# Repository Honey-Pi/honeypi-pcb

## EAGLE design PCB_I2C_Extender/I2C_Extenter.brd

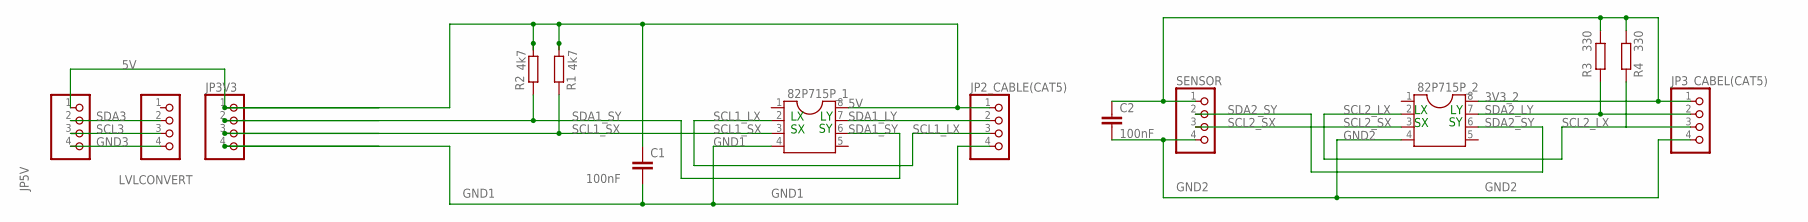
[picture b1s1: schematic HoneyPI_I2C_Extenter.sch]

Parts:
82P715P_1, 82P715P_2: DIL8; DIL08
C1, C2: 100nF; C050-045X075
JP2_CABLE(CAT5), JP3V3, JP3_CABEL(CAT5), JP5V: PINHD-1X4; 1X04
LVLCONVERT: PINHD-1X4; 1X04
R1, R2: 4k7; 0207/7
R3, R4: 330; 0207/7
SENSOR: PINHD-1X4; 1X04

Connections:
3V3_2: 82P715P_2.8, C2.1, JP3_CABEL(CAT5).1, R3.1, R4.1, SENSOR.1
5V: 82P715P_1.8, C1.1, JP2_CABLE(CAT5).1, JP3V3.1, JP5V.1, R1.1, R2.1
GND1: 82P715P_1.4, C1.2, JP2_CABLE(CAT5).4, JP3V3.4
GND2: 82P715P_2.4, C2.2, JP3_CABEL(CAT5).4, SENSOR.4
GND3: JP5V.4, LVLCONVERT.4
SCL1_LX: 82P715P_1.2, JP2_CABLE(CAT5).3
SCL1_SX: 82P715P_1.3, JP3V3.3, R1.2
SCL2_LX: 82P715P_2.2, JP3_CABEL(CAT5).3, R4.2
SCL2_SX: 82P715P_2.3, SENSOR.3
SCL3: JP5V.3, LVLCONVERT.3
SDA1_LY: 82P715P_1.7, JP2_CABLE(CAT5).2
SDA1_SY: 82P715P_1.6, JP3V3.2, R2.2
SDA2_LY: 82P715P_2.7, JP3_CABEL(CAT5).2, R3.2
SDA2_SY: 82P715P_2.6, SENSOR.2
SDA3: JP5V.2, LVLCONVERT.2

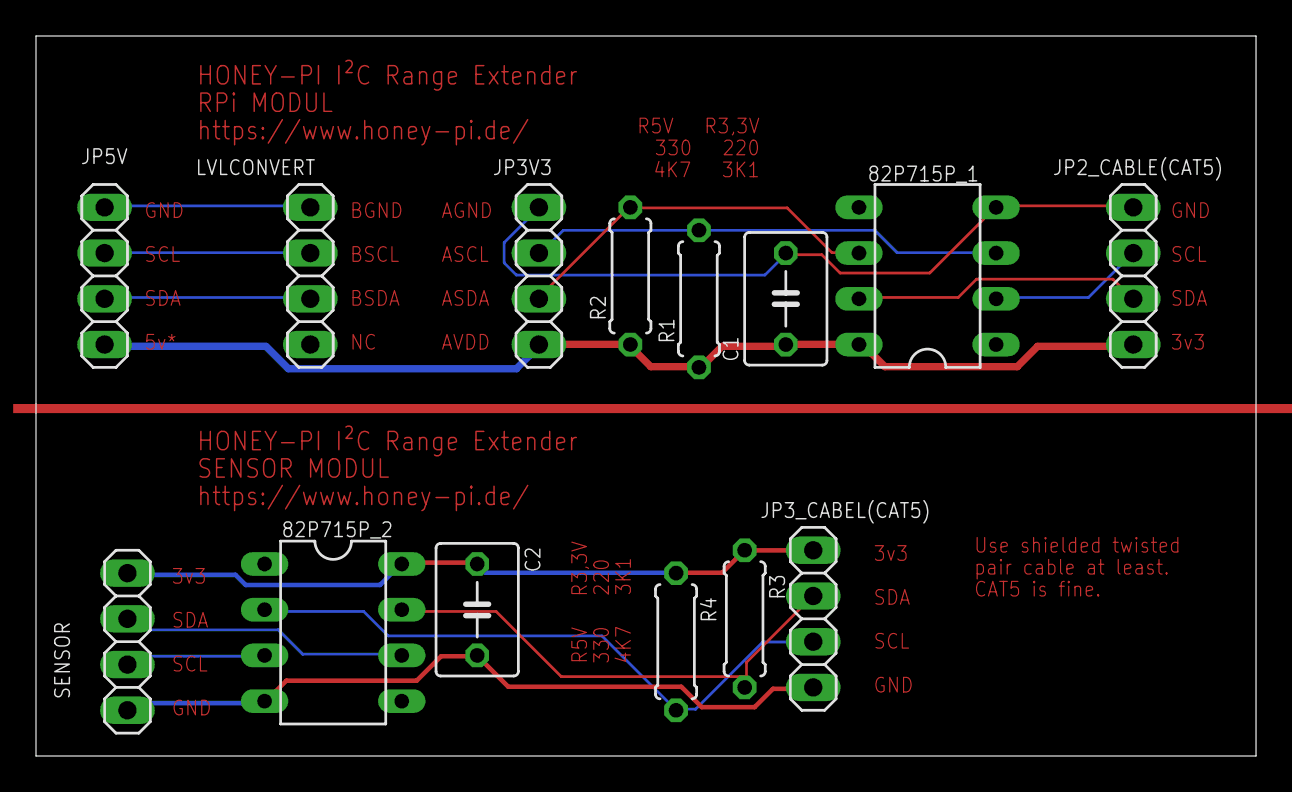
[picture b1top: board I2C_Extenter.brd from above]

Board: 2 copper layers, 67.8 x 40.0 mm, 14 parts (0 on the bottom side), 15 nets.

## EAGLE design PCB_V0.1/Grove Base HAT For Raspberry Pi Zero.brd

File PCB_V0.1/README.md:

# honeypi-pcb V0.1

Printed circuit board (PCB) for the Raspberry Pi to connect various sensors. To avoid the use of jumper cables.

## V0.1 [link](./PCB_V0.1)
Check out this [blogpost](https://www.honey-pi.de/teil-3-adapter-lk-fuer-grove-stecker/) about the grove connector board for the Raspberry Zero.
You can upload the [gerber file](./Grove%20Base%20HAT%20For%20Raspberry%20Pi%20Zero_2019-01-13.zip) to [this manufactory service](https://jlcpcb.com/quote). 10 pieces of this board cost about 7 € with delivery. 

### Pictures

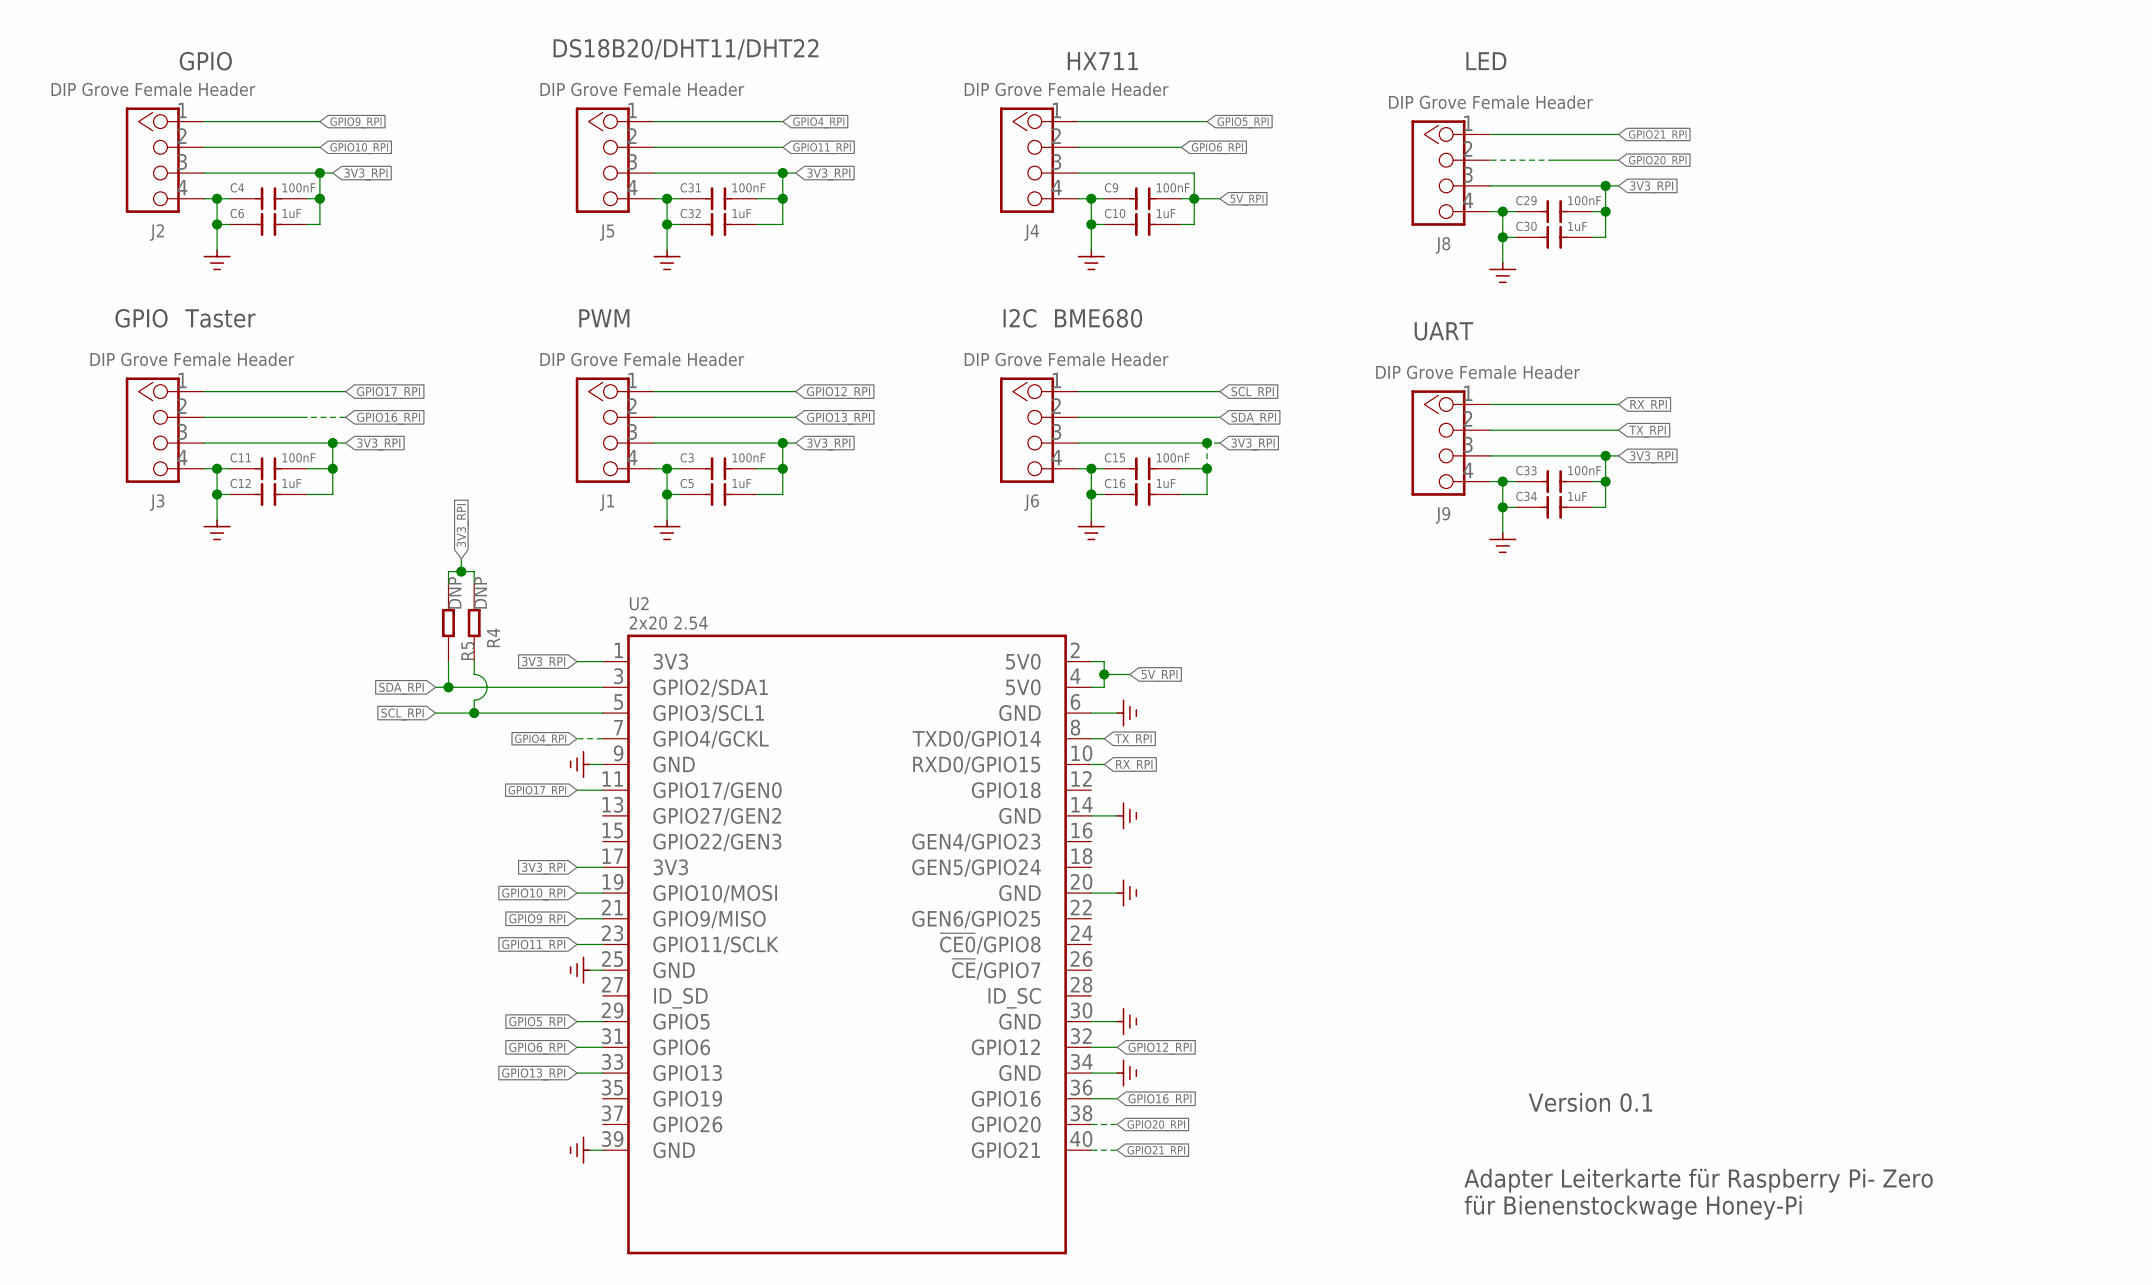
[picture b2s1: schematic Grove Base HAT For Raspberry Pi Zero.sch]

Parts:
C3, C4, C9, C11, C15, C29, C31, C33: 100nF; C0603
C5, C6, C10, C12, C16, C30, C32, C34: 1uF; C0603
J1, J2, J3, J4, J5, J6, J8, J9: DIP Grove Female Header; HW4-2.0
R4, R5: DNP; R0603
U2: 2x20 2.54; RASPBERRYPI_BASTELSTUBE_V13_RASPI_BOARD_B+_FULL

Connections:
3V3_RPI: C3.2, C4.2, C5.2, C6.2, C11.2, C12.2, C15.2, C16.2, C29.2, C30.2, C31.2, C32.2, C33.2, C34.2, J1.3, J2.3, J3.3, J5.3, J6.3, J8.3, J9.3, R4.2, R5.2, U2.1 (3V3), U2.17 (3V3)
5V_RPI: C9.2, C10.2, J4.3, U2.2 (5V0), U2.4 (5V0)
GND: C3.1, C4.1, C5.1, C6.1, C9.1, C10.1, C11.1, C12.1, C15.1, C16.1, C29.1, C30.1, C31.1, C32.1, C33.1, C34.1, J1.4, J2.4, J3.4, J4.4, J5.4, J6.4, J8.4, J9.4, U2.6 (GND), U2.9 (GND), U2.14 (GND), U2.20 (GND), U2.25 (GND), U2.30 (GND), U2.34 (GND), U2.39 (GND)
GPIO4_RPI: J5.1, U2.7 (GPIO4/GCKL)
GPIO5_RPI: J4.1, U2.29 (GPIO5)
GPIO6_RPI: J4.2, U2.31 (GPIO6)
GPIO9_RPI: J2.1, U2.21 (GPIO9/MISO)
GPIO10_RPI: J2.2, U2.19 (GPIO10/MOSI)
GPIO11_RPI: J5.2, U2.23 (GPIO11/SCLK)
GPIO12_RPI: J1.1, U2.32 (GPIO12)
GPIO13_RPI: J1.2, U2.33 (GPIO13)
GPIO16_RPI: J3.2, U2.36 (GPIO16)
GPIO17_RPI: J3.1, U2.11 (GPIO17/GEN0)
GPIO20_RPI: J8.2, U2.38 (GPIO20)
GPIO21_RPI: J8.1, U2.40 (GPIO21)
RX_RPI: J9.1, U2.10 (RXD0/GPIO15)
SCL_RPI: J6.1, R4.1, U2.5 (GPIO3/SCL1)
SDA_RPI: J6.2, R5.1, U2.3 (GPIO2/SDA1)
TX_RPI: J9.2, U2.8 (TXD0/GPIO14)

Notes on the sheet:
PWM
GPIO
UART
I2C
Version 0.1
Adapter Leiterkarte für Raspberry Pi- Zero für Bienenstockwage Honey-Pi
HX711
Taster
LED
DS18B20/DHT11/DHT22
BME680

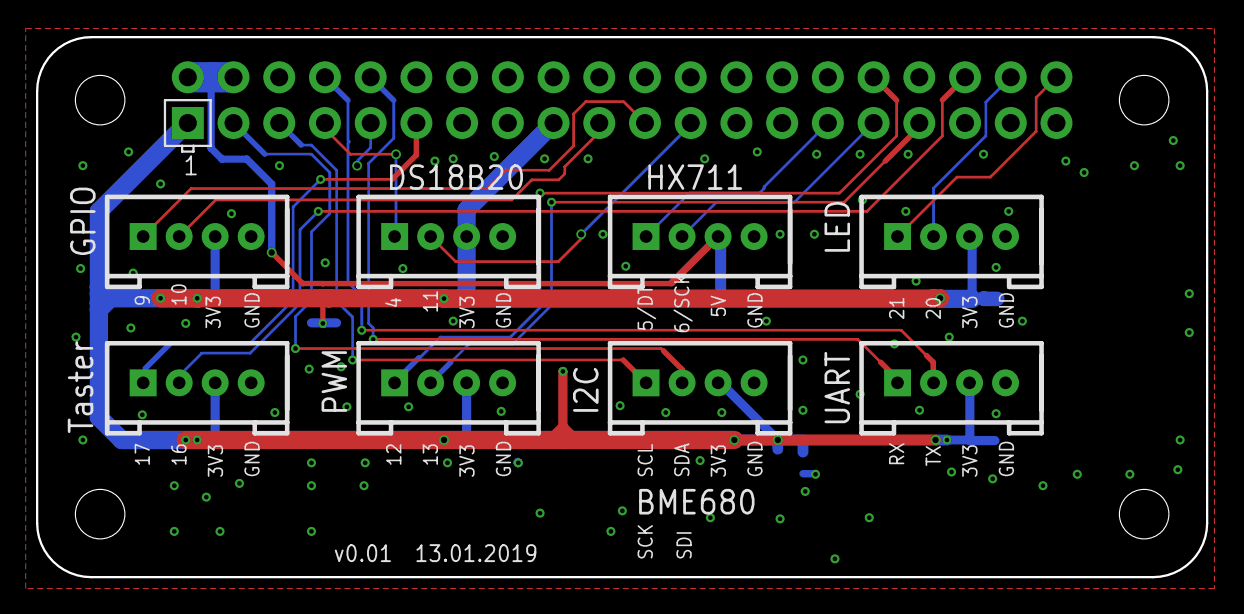
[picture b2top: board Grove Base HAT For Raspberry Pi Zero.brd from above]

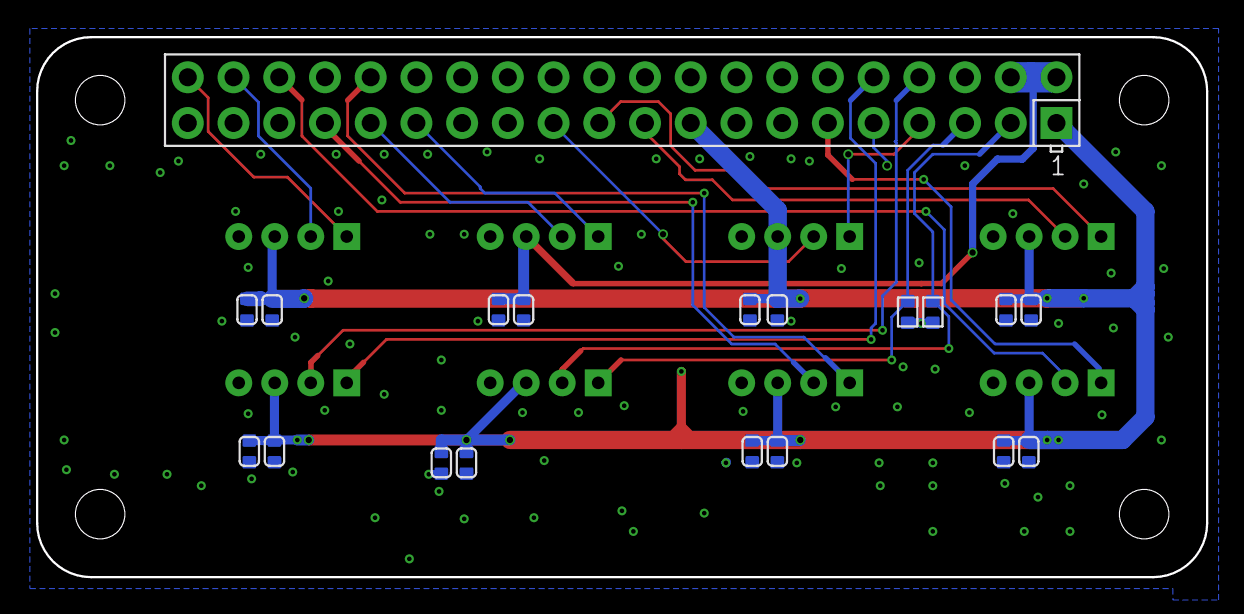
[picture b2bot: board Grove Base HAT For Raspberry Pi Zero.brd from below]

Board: 2 copper layers, 65.0 x 30.0 mm, 27 parts (18 on the bottom side), 19 nets.

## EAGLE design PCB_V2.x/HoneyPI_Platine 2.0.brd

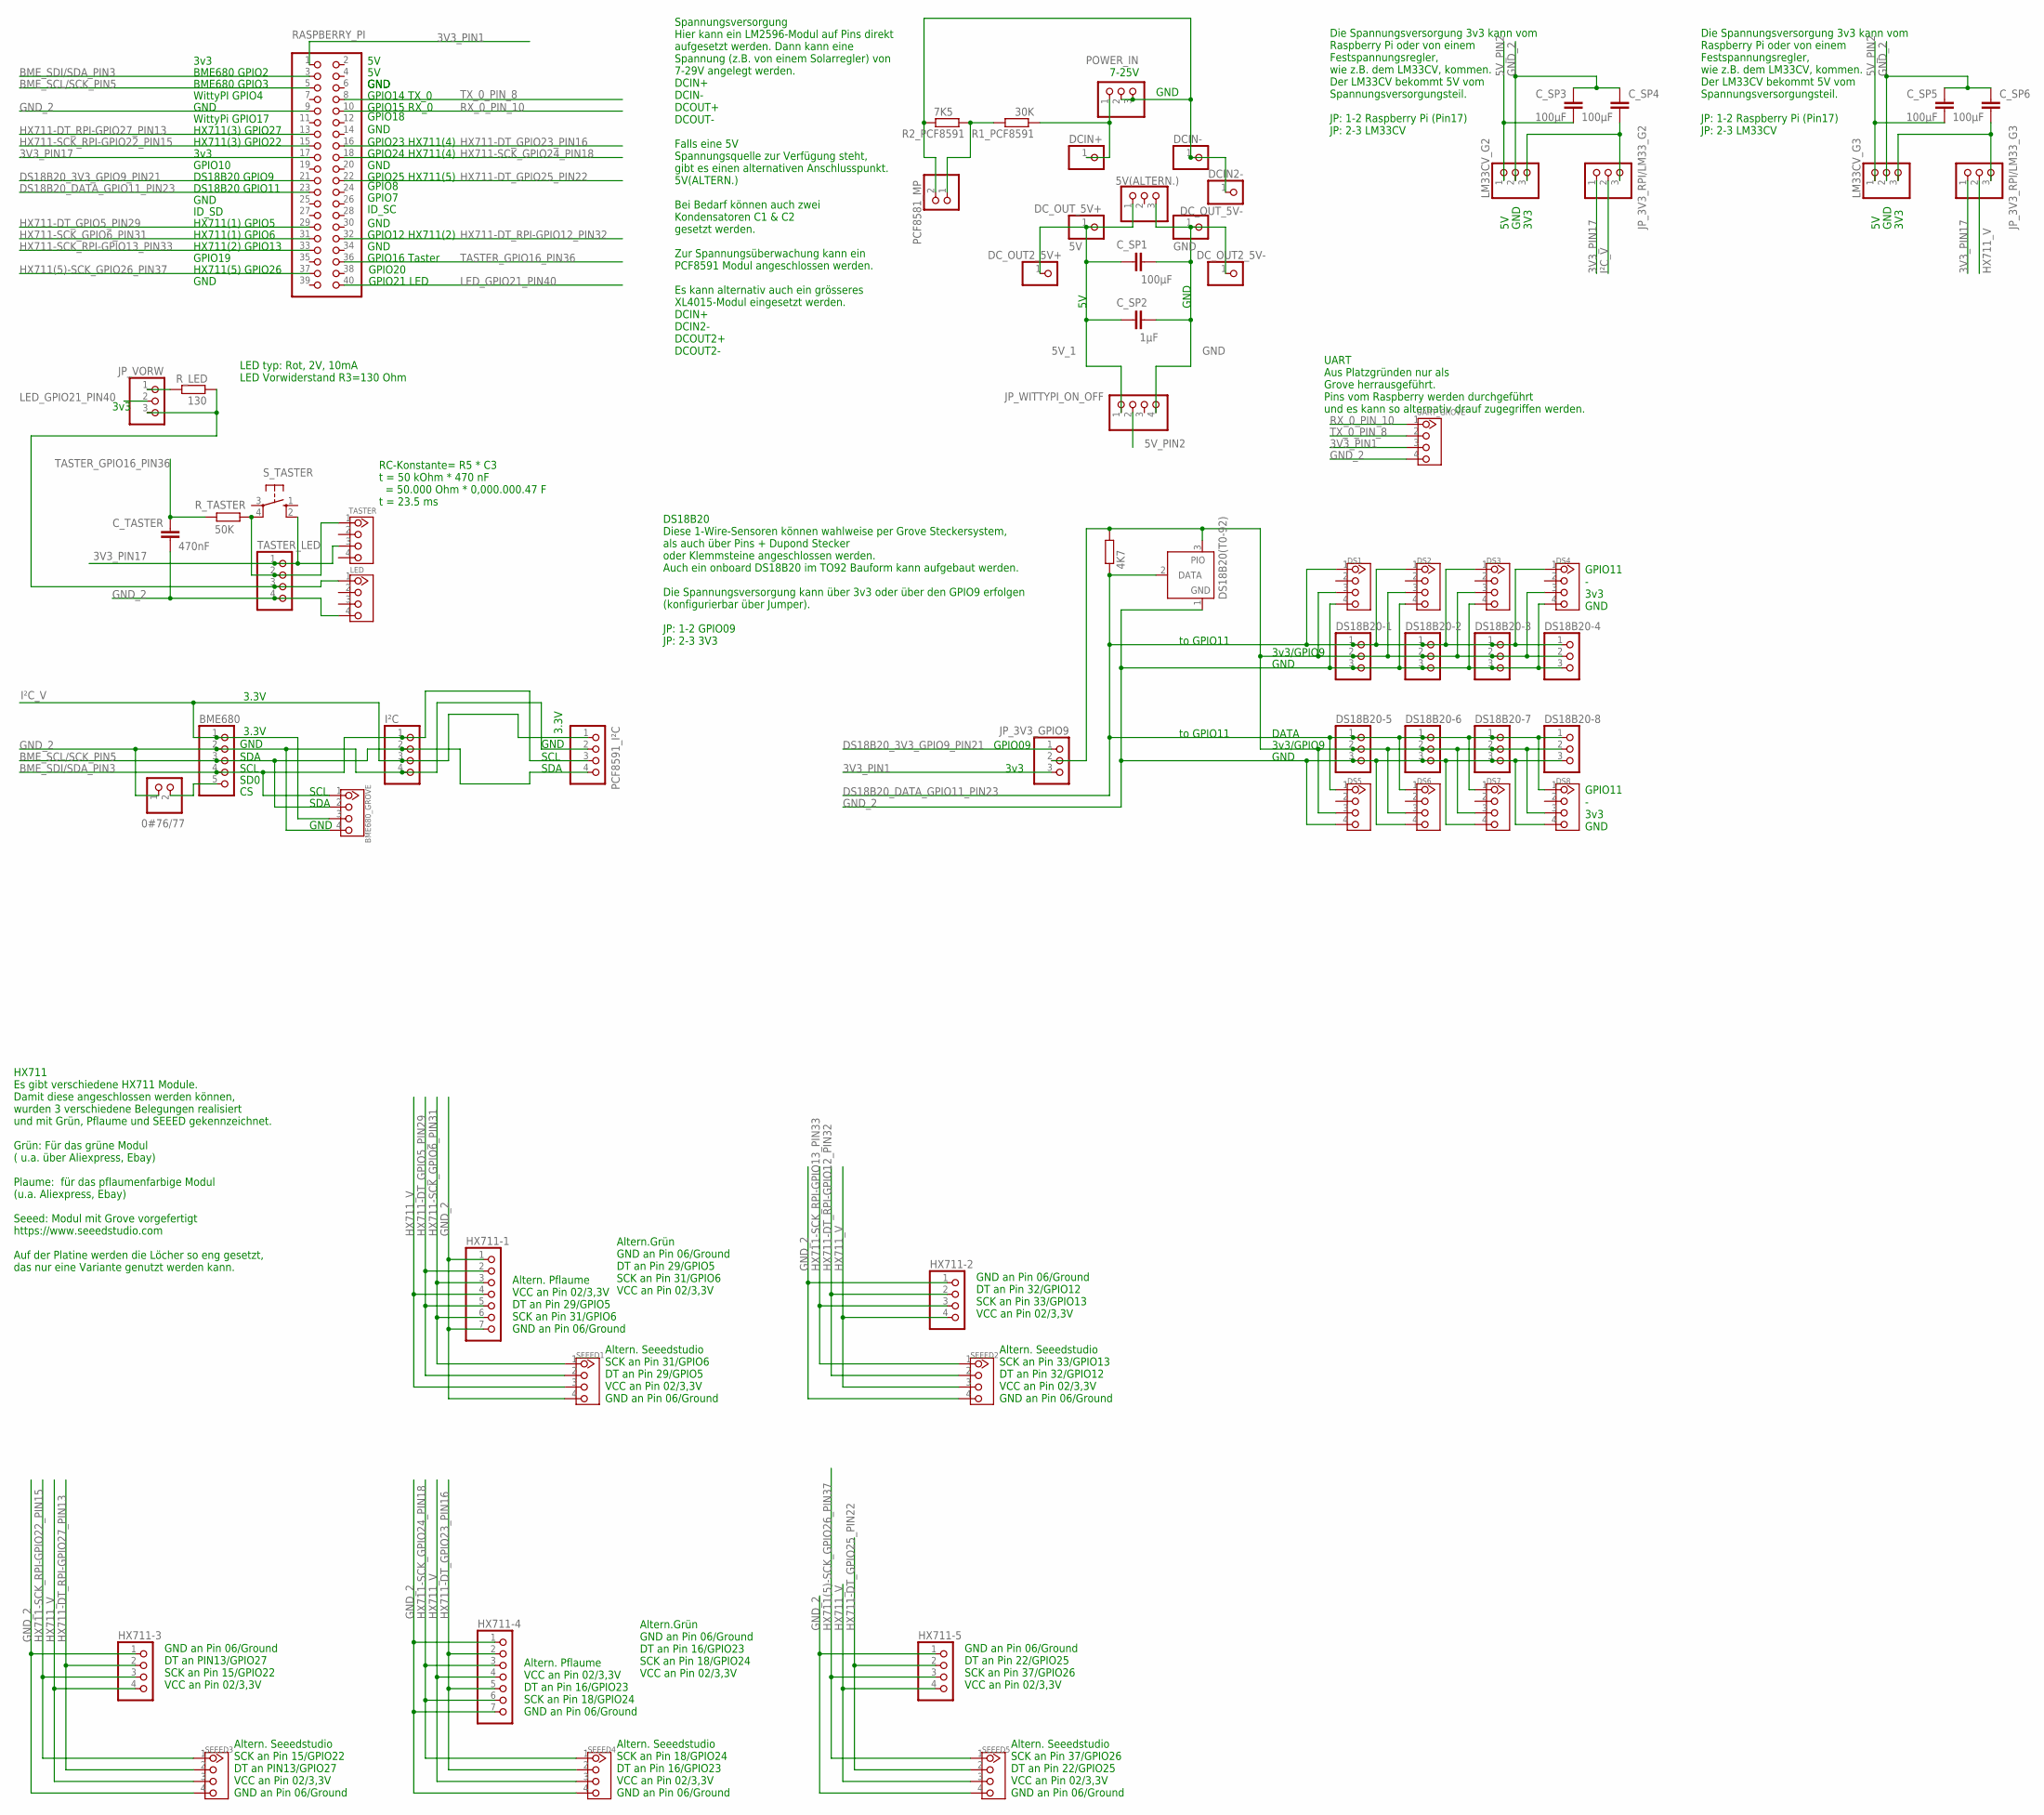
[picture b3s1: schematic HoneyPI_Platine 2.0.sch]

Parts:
0#76/77: PINHD-1X2; 1X02
5V(ALTERN.): PINHD-1X3; 1X03
BME680: PINHD-1X5; 1X05
BME680_GROVE: TWIG-4P-2.0-2.0; 4P-2.0
C_SP1, C_SP3, C_SP4, C_SP5, C_SP6: 100µF; C2.5-3
C_SP2: 1µF; C2.5-3
C_TASTER: 470nF; C2.5-3
DCIN2-: PINHD-1X1; 1X01
DCIN+: PINHD-1X1; 1X01
DCIN-: PINHD-1X1; 1X01
DC_OUT2_5V+, DC_OUT2_5V-: PINHD-1X1; 1X01
DC_OUT_5V+: 5V; 1X01
DC_OUT_5V-: GND; 1X01
DS1, DS2, DS3, DS4, DS5, DS6, DS7, DS8: TWIG-4P-2.0-2.0; 4P-2.0
DS18B20(T0-92): DS18b20; TO92-
DS18B20-1, DS18B20-2, DS18B20-3, DS18B20-4, DS18B20-5, DS18B20-6, DS18B20-7, DS18B20-8: PINHD-1X3; 1X03
HX711-1, HX711-4: PINHD-1X7; 1X07
HX711-2, HX711-3, HX711-5: PINHD-1X4; 1X04
I²C: PINHD-1X4; 1X04
JP_3V3_GPIO9, JP_3V3_RPI/LM33_G2, JP_3V3_RPI/LM33_G3: PINHD-1X3; 1X03
JP_VORW: PINHD-1X3; 1X03
JP_WITTYPI_ON_OFF: PINHD-1X4; 1X04
LED: TWIG-4P-2.0-2.0; 4P-2.0
LM33CV_G2, LM33CV_G3: PINHD-1X3; 1X03
PCF8581_MP: PINHD-1X2; 1X02
PCF8591_I²C: PINHD-1X4; 1X04
POWER_IN: PINHD-1X3; 1X03
R1_PCF8591: 30K; 0204/7
R2_PCF8591: 7K5; 0204/7
RASPBERRY_PI: PINHD-2X20; 2X20
R_DS18B20: 4K7; 0204/7
R_LED: 130; 0204/7
R_TASTER: 50K; 0204/7
SEEED1, SEEED2, SEEED3, SEEED4, SEEED5: TWIG-4P-2.0-2.0; 4P-2.0
S_TASTER: 10-XX; B3F-10XX
TASTER: TWIG-4P-2.0-2.0; 4P-2.0
TASTER_LED: PINHD-1X4; 1X04
UART_GROVE: TWIG-4P-2.0-2.0; 4P-2.0

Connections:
3V3: DS1.3, DS2.3, DS3.3, DS4.3, DS5.3, DS6.3, DS7.3, DS8.3, DS18B20(T0-92).3 (PIO), DS18B20-1.2, DS18B20-2.2, DS18B20-3.2, DS18B20-4.2, DS18B20-5.2, DS18B20-6.2, DS18B20-7.2, DS18B20-8.2, JP_3V3_GPIO9.2, R_DS18B20.2
3V3_PIN1: JP_3V3_GPIO9.3, RASPBERRY_PI.1, UART_GROVE.3
3V3_PIN17: JP_3V3_RPI/LM33_G2.1, JP_3V3_RPI/LM33_G3.1, RASPBERRY_PI.17, S_TASTER.2 (S1), TASTER.3, TASTER_LED.1
5V_1: 5V(ALTERN.).1, C_SP1.1, C_SP2.1, DC_OUT2_5V+.1, DC_OUT_5V+.1, JP_WITTYPI_ON_OFF.1
5V_PIN2: C_SP3.1, C_SP5.1, JP_WITTYPI_ON_OFF.2, LM33CV_G2.1, LM33CV_G3.1
BME_SCL/SCK_PIN5: BME680.3, BME680_GROVE.2, I²C.2, PCF8591_I²C.4, RASPBERRY_PI.5
BME_SDI/SDA_PIN3: BME680.4, BME680_GROVE.1, I²C.1, PCF8591_I²C.3, RASPBERRY_PI.3
DS18B20_3V3_GPIO9_PIN21: JP_3V3_GPIO9.1, RASPBERRY_PI.21
DS18B20_DATA_GPIO11_PIN23: DS1.1, DS2.1, DS3.1, DS4.1, DS5.1, DS6.1, DS7.1, DS8.1, DS18B20(T0-92).2 (DATA), DS18B20-1.1, DS18B20-2.1, DS18B20-3.1, DS18B20-4.1, DS18B20-5.1, DS18B20-6.1, DS18B20-7.1, DS18B20-8.1, RASPBERRY_PI.23, R_DS18B20.1
GND: 5V(ALTERN.).3, C_SP1.2, C_SP2.2, DC_OUT2_5V-.1, DC_OUT_5V-.1, JP_WITTYPI_ON_OFF.4
GND_2: 0#76/77.1, BME680.2, BME680_GROVE.4, C_SP3.2, C_SP4.2, C_SP5.2, C_SP6.2, C_TASTER.1, DS1.4, DS2.4, DS3.4, DS4.4, DS5.4, DS6.4, DS7.4, DS8.4, DS18B20(T0-92).1 (GND), DS18B20-1.3, DS18B20-2.3, DS18B20-3.3, DS18B20-4.3, DS18B20-5.3, DS18B20-6.3, DS18B20-7.3, DS18B20-8.3, HX711-1.1, HX711-1.7, HX711-2.1, HX711-3.1, HX711-4.1, HX711-4.7, HX711-5.1, I²C.4, LED.4, LM33CV_G2.2, LM33CV_G3.2, PCF8591_I²C.2, RASPBERRY_PI.9, SEEED1.4, SEEED2.4, SEEED3.4, SEEED4.4, SEEED5.4, TASTER_LED.4, UART_GROVE.4
HX711(5)-SCK_GPIO26_PIN37: HX711-5.3, RASPBERRY_PI.37, SEEED5.1
HX711-DT_GPIO5_PIN29: HX711-1.2, HX711-1.5, RASPBERRY_PI.29, SEEED1.2
HX711-DT_GPIO23_PIN16: HX711-4.2, HX711-4.5, RASPBERRY_PI.16, SEEED4.2
HX711-DT_GPIO25_PIN22: HX711-5.2, RASPBERRY_PI.22, SEEED5.2
HX711-DT_RPI-GPIO12_PIN32: HX711-2.2, RASPBERRY_PI.32, SEEED2.2
HX711-DT_RPI-GPIO27_PIN13: HX711-3.2, RASPBERRY_PI.13, SEEED3.2
HX711-SCK_GPIO6_PIN31: HX711-1.3, HX711-1.6, RASPBERRY_PI.31, SEEED1.1
HX711-SCK_GPIO24_PIN18: HX711-4.3, HX711-4.6, RASPBERRY_PI.18, SEEED4.1
HX711-SCK_RPI-GPIO13_PIN33: HX711-2.3, RASPBERRY_PI.33, SEEED2.1
HX711-SCK_RPI-GPIO22_PIN15: HX711-3.3, RASPBERRY_PI.15, SEEED3.1
HX711_V: HX711-1.4, HX711-2.4, HX711-3.4, HX711-4.4, HX711-5.4, JP_3V3_RPI/LM33_G3.2, SEEED1.3, SEEED2.3, SEEED3.3, SEEED4.3, SEEED5.3
I²C_V: BME680.1, BME680_GROVE.3, I²C.3, JP_3V3_RPI/LM33_G2.2, PCF8591_I²C.1
LED_2: JP_VORW.3, LED.1, R_LED.2, TASTER_LED.3
LED_GPIO21_PIN40: JP_VORW.2, RASPBERRY_PI.40
unnamed: DCIN2-.1, DCIN-.1, PCF8581_MP.2, POWER_IN.2, POWER_IN.3, R2_PCF8591.2
unnamed: C_SP4.1, JP_3V3_RPI/LM33_G2.3, LM33CV_G2.3
unnamed: R_TASTER.1, S_TASTER.4 (P1), TASTER.1, TASTER_LED.2
unnamed: C_SP6.1, JP_3V3_RPI/LM33_G3.3, LM33CV_G3.3
unnamed: PCF8581_MP.1, R1_PCF8591.2, R2_PCF8591.1
unnamed: 0#76/77.2, BME680.5
unnamed: JP_VORW.1, R_LED.1
unnamed: DCIN+.1, POWER_IN.1, R1_PCF8591.1
RX_0_PIN_10: RASPBERRY_PI.10, UART_GROVE.1
TASTER_GPIO16_PIN36: C_TASTER.2, RASPBERRY_PI.36, R_TASTER.2
TX_0_PIN_8: RASPBERRY_PI.8, UART_GROVE.2

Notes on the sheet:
3v3
3v3/GPIO9
DATA
GND
SCL
SDA
SD0
7-25V
Altern. Pflaume VCC an Pin 02/3,3V DT an Pin 29/GPIO5 SCK an Pin 31/GPIO6 GND an Pin 06/Ground
GPIO18
Altern.Grün GND an Pin 06/Ground DT an Pin 29/GPIO5 SCK an Pin 31/GPIO6 VCC an Pin 02/3,3V
BME680 GPIO2
BME680 GPIO3
WittyPI GPIO4
WittyPi GPIO17
DS18B20 GPIO9
DS18B20 GPIO11
HX711(1) GPIO5
HX711(1) GPIO6
HX711(2) GPIO13
GPIO16 Taster
GPIO21 LED
GPIO12 HX711(2)
to GPIO11
GPIO11 - 3v3 GND
GPIO09
GPIO23 HX711(4)
GPIO24 HX711(4)
GPIO25 HX711(5)
HX711(5) GPIO26
GPIO15 RX_0
GPIO14 TX_0
HX711(3) GPIO27
HX711(3) GPIO22
Altern. Seeedstudio SCK an Pin 31/GPIO6 DT an Pin 29/GPIO5 VCC an Pin 02/3,3V GND an Pin 06/Ground
GND an Pin 06/Ground DT an Pin 32/GPIO12 SCK an Pin 33/GPIO13 VCC an Pin 02/3,3V
Altern. Seeedstudio SCK an Pin 33/GPIO13 DT an Pin 32/GPIO12 VCC an Pin 02/3,3V GND an Pin 06/Ground
GND an Pin 06/Ground DT an PIN13/GPIO27 SCK an Pin 15/GPIO22 VCC an Pin 02/3,3V
Altern. Seeedstudio SCK an Pin 15/GPIO22 DT an PIN13/GPIO27 VCC an Pin 02/3,3V GND an Pin 06/Ground
Altern. Pflaume VCC an Pin 02/3,3V DT an Pin 16/GPIO23 SCK an Pin 18/GPIO24 GND an Pin 06/Ground

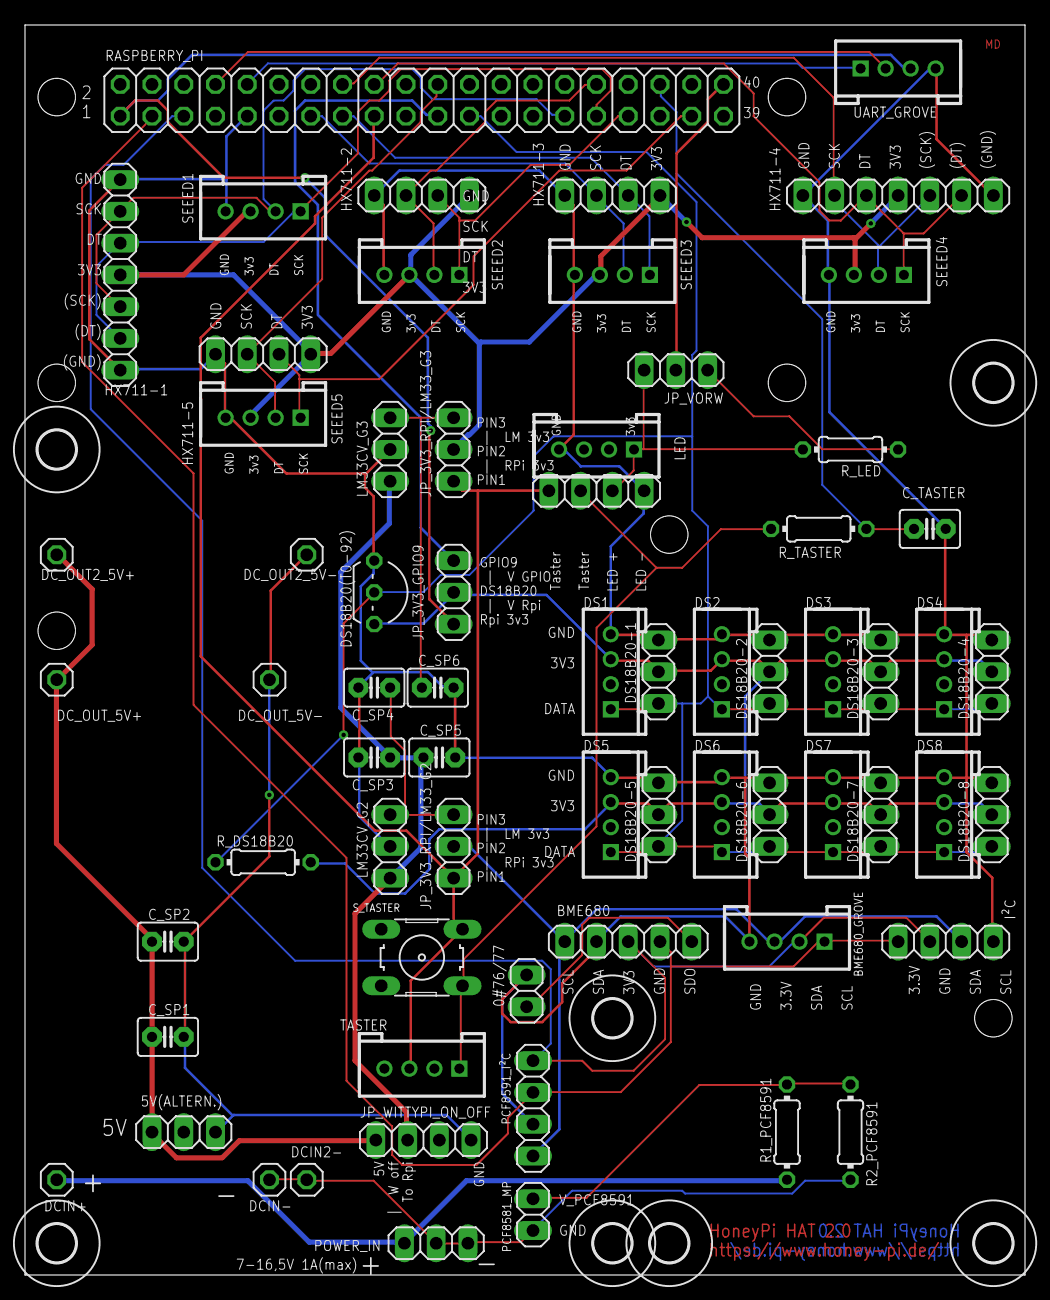
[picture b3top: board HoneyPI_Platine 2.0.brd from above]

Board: 2 copper layers, 80.0 x 100.0 mm, 74 parts (0 on the bottom side), 36 nets.

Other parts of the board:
U$1, U$2, U$3, U$4, U$5, U$6, U$8: 3,0

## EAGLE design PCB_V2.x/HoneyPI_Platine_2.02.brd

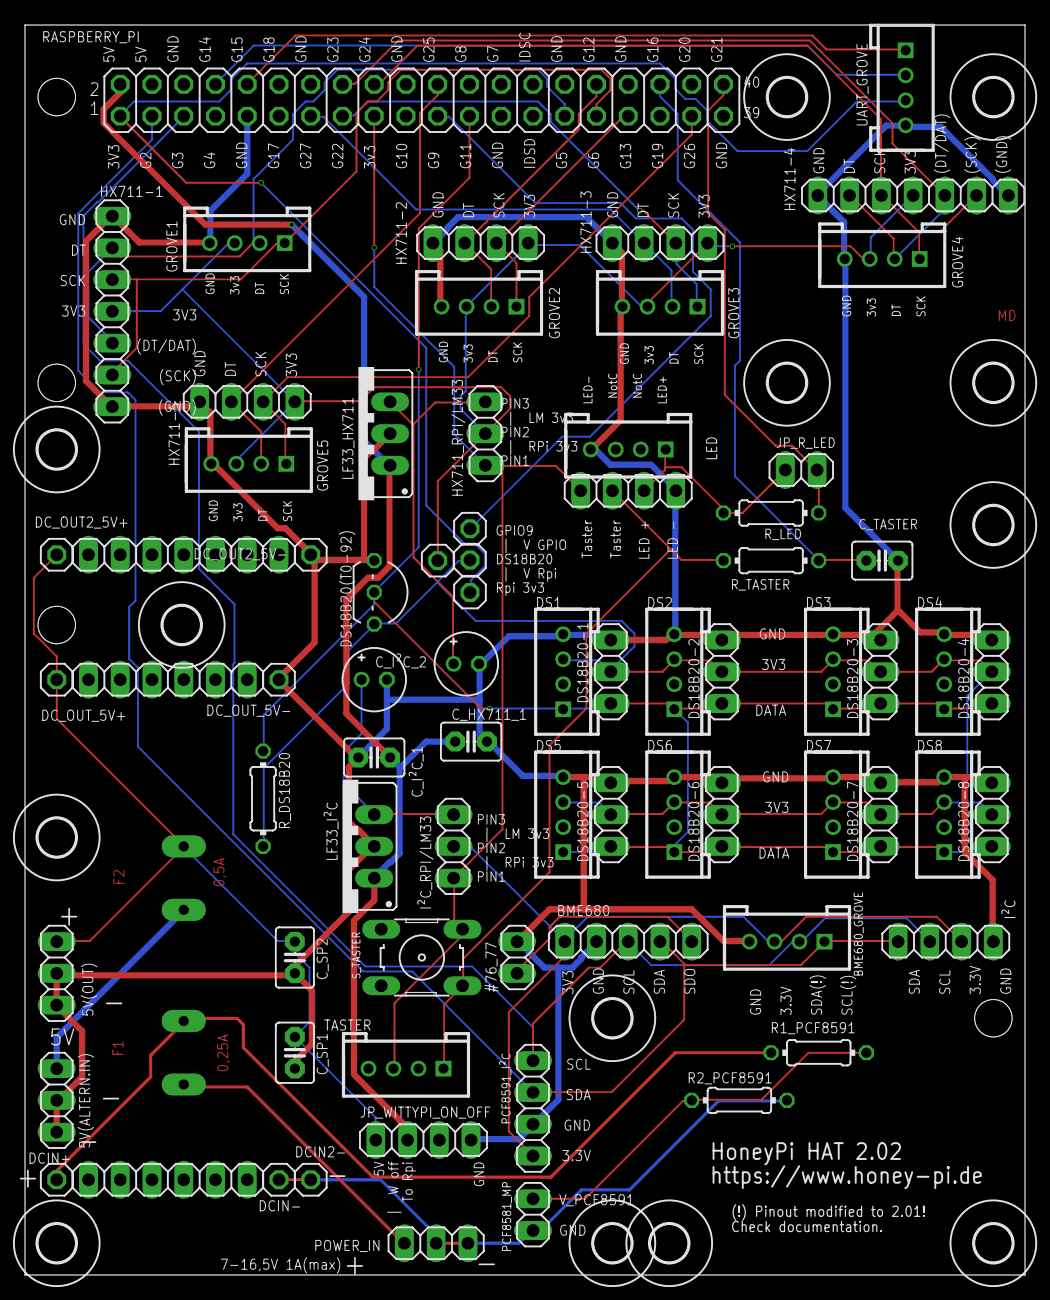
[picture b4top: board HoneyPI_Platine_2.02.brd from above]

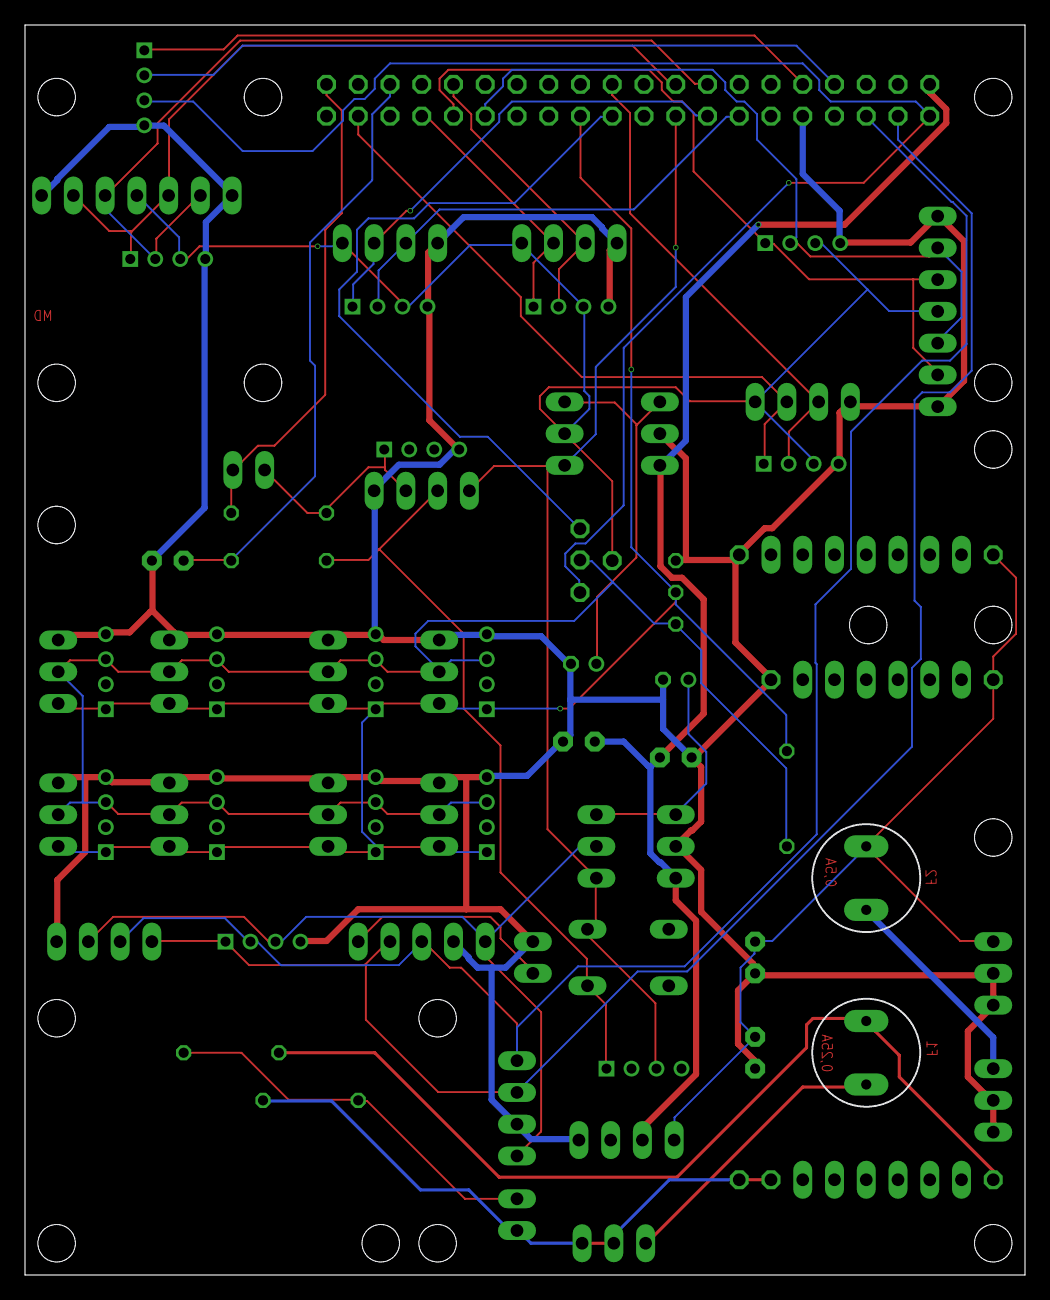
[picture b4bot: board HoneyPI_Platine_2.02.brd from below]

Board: 2 copper layers, 80.0 x 100.0 mm, 89 parts (2 on the bottom side), 36 nets.

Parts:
5V(ALTERN.IN), 5V(OUT): 1X03
#76_77: 1X02
BME680: 1X05
BME680_GROVE: 4P-2.0
C_HX711_1: 0,1µF; C2.5-3
C_HX711_2: 10µF; E2-5
C_I²C_1: 0,1µF; C2.5-3
C_I²C_2: 10µF; E2-5
C_SP1: xxµF; C2.5-3
C_SP2: xµF; C2.5-3
C_TASTER: 100nF; C2.5-3
DCIN2-: 1X01
DCIN+: 1X01
DCIN-: 1X01
DC_OUT2_5V+, DC_OUT2_5V-: 1X01
DC_OUT_5V+: 5V; 1X01
DC_OUT_5V-: GND; 1X01
DS1, DS2, DS3, DS4, DS5, DS6, DS7, DS8: 4P-2.0
DS18B20(T0-92): DS18b20; TO92-
DS18B20-1, DS18B20-2, DS18B20-3, DS18B20-4, DS18B20-5, DS18B20-6, DS18B20-7, DS18B20-8: 1X03
F1: 0,25A; TR5
F2: 0,5A; TR5
GROVE1, GROVE2, GROVE3, GROVE4, GROVE5: 4P-2.0
HX, HX1, HX2, HX3: 1X01
HX711-1, HX711-4: 1X07
HX711-2, HX711-3, HX711-5: 1X04
HX711_RPI/LM33: 1X03
I²C: 1X04
I²C_RPI/LM33: 1X03
JP1: 1X07
JP2, JP3: 1X06
JP_R_LED: 1X02
JP_WITTYPI_ON_OFF: 1X04
LED: 4P-2.0
LF33_HX711, LF33_I²C: 337TS
PCF8581_MP: 1X02
PCF8591_I²C: 1X04
POWER_IN: 1X03
R1_PCF8591: 30K; 0204/7
R2_PCF8591: 7K5; 0204/7
RASPBERRY_PI: 2X20
R_DS18B20: 4K7; 0204/7
R_LED: 130Ohm; 0204/7
R_TASTER: 47K; 0204/7
S_TASTER: B3F-10XX
TASTER: 4P-2.0
TASTER_LED: 1X04
U$1, U$2, U$3, U$4, U$5, U$6, U$7, U$8, U$9, U$10, U$11, U$12, U$13: 3,0
UART_GROVE: 4P-2.0

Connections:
3V3: DS1.3, DS2.3, DS3.3, DS4.3, DS5.3, DS6.3, DS7.3, DS8.3, DS18B20(T0-92).3, DS18B20-1.2, DS18B20-2.2, DS18B20-3.2, DS18B20-4.2, DS18B20-5.2, DS18B20-6.2, DS18B20-7.2, DS18B20-8.2, HX2.1, R_DS18B20.2
3V3_PIN1: HX3.1, RASPBERRY_PI.1, UART_GROVE.3
3V3_PIN17: HX711_RPI/LM33.1, I²C_RPI/LM33.1, RASPBERRY_PI.17, S_TASTER.2, TASTER.3, TASTER_LED.1
5V_1: 5V(OUT).1, C_SP1.1, C_SP2.1, DC_OUT2_5V+.1, DC_OUT_5V+.1, F2.1, JP_WITTYPI_ON_OFF.1
5V_PIN2: C_HX711_1.1, C_I²C_1.1, JP_WITTYPI_ON_OFF.2, LF33_HX711.1, LF33_I²C.1, RASPBERRY_PI.2
BME_SCL/SCK_PIN5: BME680.3, BME680_GROVE.1, I²C.2, PCF8591_I²C.4, RASPBERRY_PI.5
BME_SDI/SDA_PIN3: BME680.4, BME680_GROVE.2, I²C.1, PCF8591_I²C.3, RASPBERRY_PI.3
DS18B20_3V3_GPIO9_PIN21: HX1.1, RASPBERRY_PI.21
DS18B20_DATA_GPIO11_PIN23: DS1.1, DS2.1, DS3.1, DS4.1, DS5.1, DS6.1, DS7.1, DS8.1, DS18B20(T0-92).2, DS18B20-1.1, DS18B20-2.1, DS18B20-3.1, DS18B20-4.1, DS18B20-5.1, DS18B20-6.1, DS18B20-7.1, DS18B20-8.1, RASPBERRY_PI.23, R_DS18B20.1
GND: 5V(ALTERN.IN).2, 5V(ALTERN.IN).3, 5V(OUT).2, 5V(OUT).3, #76_77.2, BME680.2, BME680_GROVE.4, C_HX711_1.2, C_HX711_2.-, C_I²C_1.2, C_I²C_2.-, C_SP1.2, C_SP2.2, C_TASTER.1, DC_OUT2_5V-.1, DC_OUT_5V-.1, DS1.4, DS2.4, DS3.4, DS4.4, DS5.4, DS6.4, DS7.4, DS8.4, DS18B20(T0-92).1, DS18B20-1.3, DS18B20-2.3, DS18B20-3.3, DS18B20-4.3, DS18B20-5.3, DS18B20-6.3, DS18B20-7.3, DS18B20-8.3, GROVE1.4, GROVE2.4, GROVE3.4, GROVE4.4, GROVE5.4, HX711-1.1, HX711-1.7, HX711-2.1, HX711-3.1, HX711-4.1, HX711-4.7, HX711-5.1, I²C.4, JP_WITTYPI_ON_OFF.4, LED.4, LF33_HX711.2, LF33_I²C.2, PCF8591_I²C.2, RASPBERRY_PI.9, TASTER_LED.4, UART_GROVE.4
GND20V: DCIN2-.1, DCIN-.1, PCF8581_MP.2, POWER_IN.2, POWER_IN.3, R2_PCF8591.2
HX711(5)-SCK_GPIO26_PIN37: GROVE5.1, HX711-5.3, RASPBERRY_PI.37
HX711-DT_GPIO5_PIN29: GROVE1.2, HX711-1.2, HX711-1.5, RASPBERRY_PI.29
HX711-DT_GPIO23_PIN16: GROVE4.2, HX711-4.2, HX711-4.5, RASPBERRY_PI.16
HX711-DT_GPIO25_PIN22: GROVE5.2, HX711-5.2, RASPBERRY_PI.22
HX711-DT_RPI-GPIO12_PIN32: GROVE2.2, HX711-2.2, RASPBERRY_PI.32
HX711-DT_RPI-GPIO27_PIN13: GROVE3.2, HX711-3.2, RASPBERRY_PI.13
HX711-SCK_GPIO6_PIN31: GROVE1.1, HX711-1.3, HX711-1.6, RASPBERRY_PI.31
HX711-SCK_GPIO24_PIN18: GROVE4.1, HX711-4.3, HX711-4.6, RASPBERRY_PI.18
HX711-SCK_RPI-GPIO13_PIN33: GROVE2.1, HX711-2.3, RASPBERRY_PI.33
HX711-SCK_RPI-GPIO22_PIN15: GROVE3.1, HX711-3.3, RASPBERRY_PI.15
HX711_V: GROVE1.3, GROVE2.3, GROVE3.3, GROVE4.3, GROVE5.3, HX.1, HX711-1.4, HX711-2.4, HX711-3.4, HX711-4.4, HX711-5.4, HX711_RPI/LM33.2
I²C_V: BME680.1, BME680_GROVE.3, I²C.3, I²C_RPI/LM33.2, PCF8591_I²C.1
LED_2: JP_R_LED.2, LED.1, R_LED.2, TASTER_LED.3
LED_GPIO21_PIN40: JP_R_LED.1, RASPBERRY_PI.40, R_LED.1
unnamed: C_I²C_2.+, I²C_RPI/LM33.3, LF33_I²C.3
unnamed: R_TASTER.1, S_TASTER.4, TASTER.1, TASTER_LED.2
unnamed: C_HX711_2.+, HX711_RPI/LM33.3, LF33_HX711.3
unnamed: #76_77.1, BME680.5
unnamed: 5V(ALTERN.IN).1, F2.2
RX_0_PIN_10: RASPBERRY_PI.10, UART_GROVE.1
SPANNUNGSTEILER1: PCF8581_MP.1, R1_PCF8591.2, R2_PCF8591.1
TASTER_GPIO16_PIN36: C_TASTER.2, RASPBERRY_PI.36, R_TASTER.2
TX_0_PIN_8: RASPBERRY_PI.8, UART_GROVE.2
VDD20V1: DCIN+.1, F1.1, R1_PCF8591.1
VDD20V2: F1.2, POWER_IN.1
